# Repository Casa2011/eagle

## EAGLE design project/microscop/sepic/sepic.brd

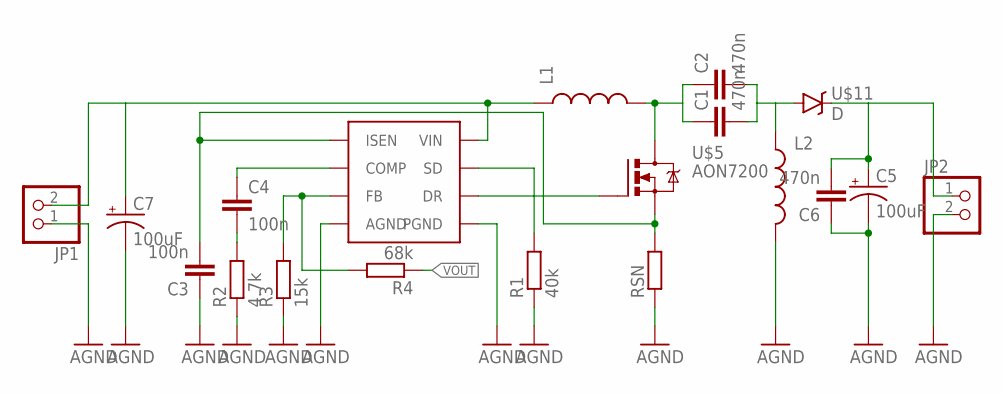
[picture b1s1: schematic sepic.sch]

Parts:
C1, C2, C6: 470n; C0805
C3, C4: 100n; C0805
C5, C7: 100uF; NIC_10X10.5_CAP
JP1, JP2: PINHD-1X02_2.54; 1X02
L1, L2: INDUCTORSRU1038; SRU1038
R1: 40k; 0603
R2: 4.7k; R0805
R3: 15k; R0805
R4: 68k; R0805
RSN: R2512
U$1: LM3488; S-PDSO-G8
U$5: AON7200; DFN3X3
U$11: D; SMA-DIODE

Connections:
AGND: C3.1, C5.-, C6.1, C7.-, JP1.1, JP2.2, L2.2, R1.1, R2.1, R3.1, RSN.P$1 (1), U$1.4 (AGND), U$1.5 (PGND)
unnamed: C3.2, RSN.P$2 (2), U$1.1 (ISEN), U$5.S:1 (S), U$5.S:2 (S), U$5.S:3 (S)
unnamed: U$1.6 (DR), U$5.G
unnamed: R1.2, U$1.7 (SD)
unnamed: C1.1, C2.1, L1.2, U$5.D, U$5.D:1 (D), U$5.D:2 (D), U$5.D:3 (D), U$5.D:4 (D), U$5.D:5 (D), U$5.D:6 (D)
unnamed: C1.2, C2.2, L2.1, U$11.A
unnamed: C4.1, U$1.2 (COMP)
unnamed: C4.2, R2.2
unnamed: R3.2, R4.2, U$1.3 (FB)
VIN: C7.+, JP1.2, L1.1, U$1.8 (VIN)
VOUT: C5.+, C6.2, JP2.1, R4.1, U$11.C

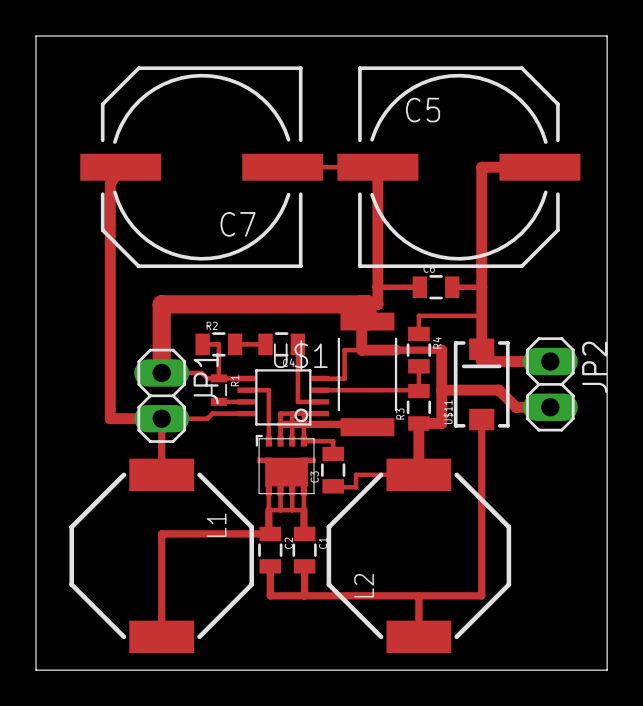
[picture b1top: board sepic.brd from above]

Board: 2 copper layers, 31.7 x 35.2 mm, 19 parts (0 on the bottom side), 11 nets.

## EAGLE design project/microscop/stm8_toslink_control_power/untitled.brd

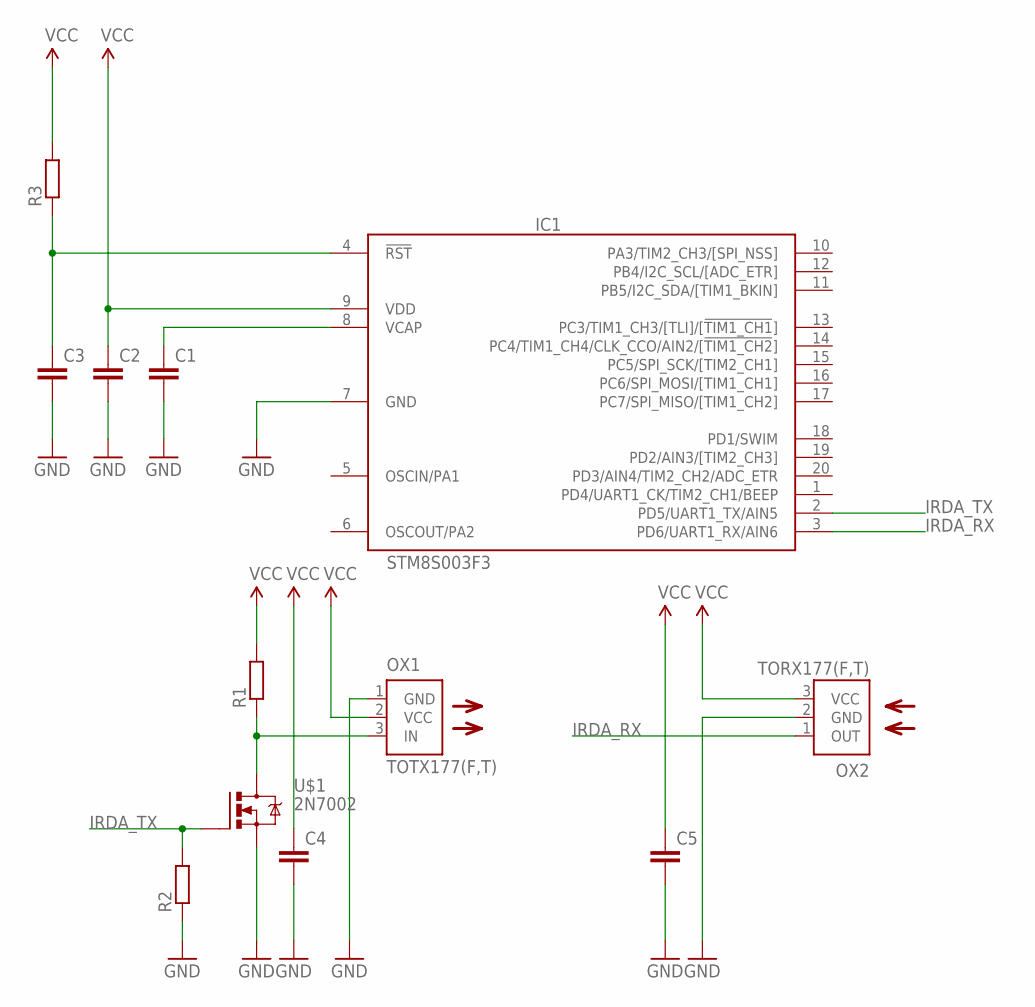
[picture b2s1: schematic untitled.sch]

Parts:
C1, C2, C4, C5: CC0805; C0805
C3: CC0603; C0603
IC1: STM8S003F3; TSSOP20
OX1: TOTX177(F,T); TOTX
OX2: TORX177(F,T); TORX
R1, R2, R3: R0603; 0603
U$1: 2N7002; SOT23

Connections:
GND: C1.2, C2.2, C3.2, C4.2, C5.2, IC1.7 (GND), OX1.1 (GND), OX2.2 (GND), R2.1, U$1.2 (S)
IRDA_RX: IC1.3 (PD6/UART1_RX/AIN6), OX2.1 (OUT)
IRDA_TX: IC1.2 (PD5/UART1_TX/AIN5), R2.2, U$1.1 (G)
unnamed: C1.1, IC1.8 (VCAP)
unnamed: OX1.3 (IN), R1.1, U$1.3 (D)
unnamed: C3.1, IC1.4 (!RST), R3.1
VCC: C2.1, C4.1, C5.1, IC1.9 (VDD), OX1.2 (VCC), OX2.3 (VCC), R1.2, R3.2

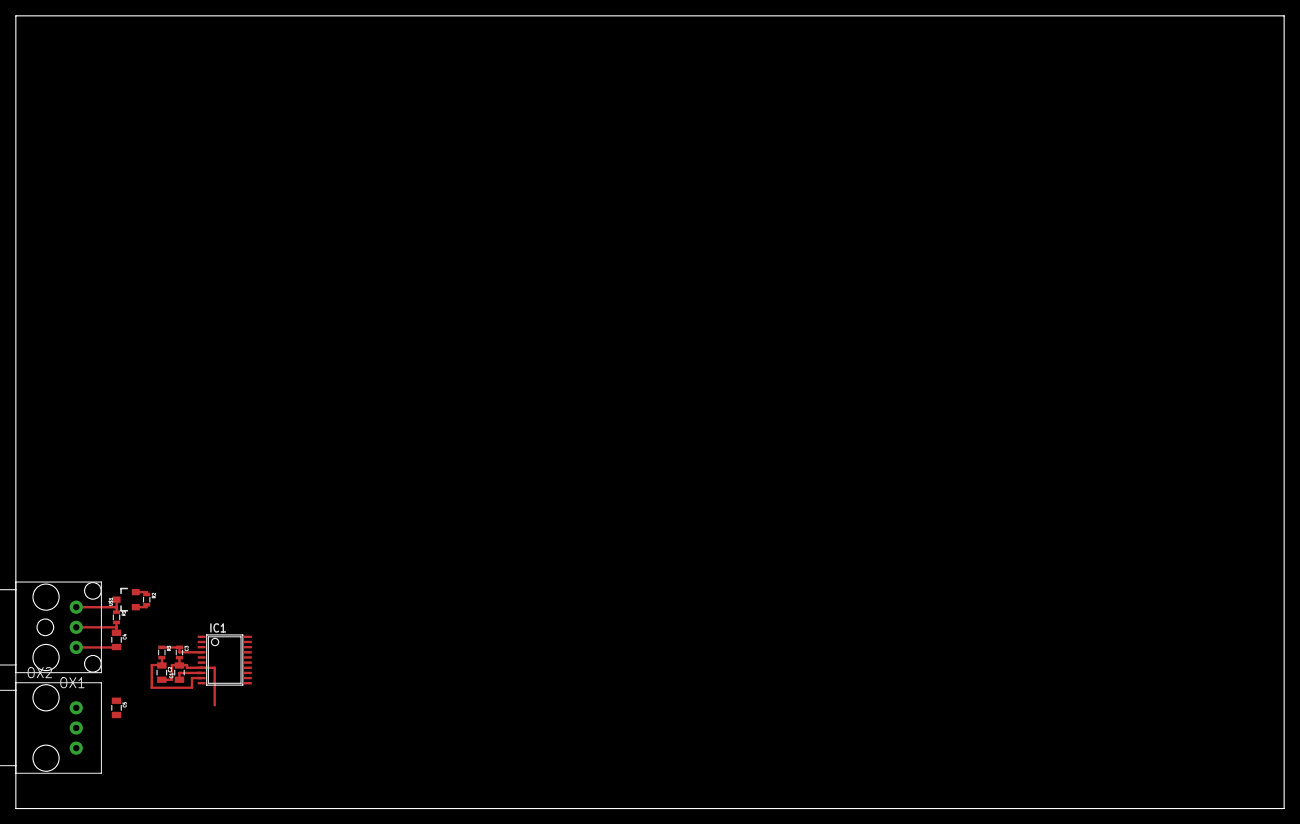
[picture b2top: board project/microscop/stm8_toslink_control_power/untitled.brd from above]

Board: 2 copper layers, 160.0 x 100.0 mm, 12 parts (0 on the bottom side), 7 nets.

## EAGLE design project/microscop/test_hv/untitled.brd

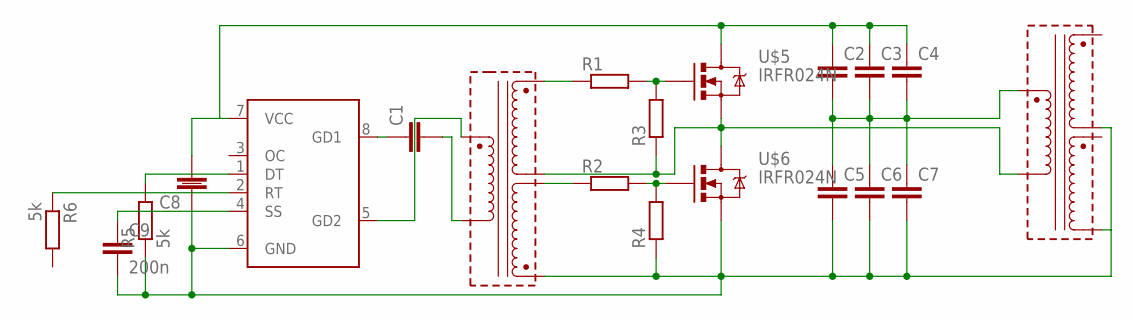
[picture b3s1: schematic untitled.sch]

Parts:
C1, C2, C3, C4, C5, C6, C7, C8: CC0805; C0805
C9: 200n; C0805
R1, R2, R3, R4: R0805
R5, R6: 5k; R0805
U$1: TPS92020; SO08
U$2: ADSL_GDT
U$3: CCFL; TRANSFORMER_HVX2
U$5, U$6: IRFR024N; D-PAK_TO252AA

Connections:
unnamed: C1.1, U$1.8 (GD1)
unnamed: C1.2, U$2.GD` (GD2)
unnamed: U$1.5 (GD2), U$2.GD (GD1)
unnamed: R1.1, U$2.OUT1 (OUT1+)
unnamed: R2.1, U$2.OUT2` (OUT2-)
unnamed: R1.2, R3.2, U$5.1 (G)
unnamed: R2.2, R4.2, U$6.1 (G)
unnamed: R3.1, U$2.OUT1` (OUT1-), U$3.P$3 (GD2), U$5.3 (S), U$6.2 (D)
unnamed: C5.2, C6.2, C7.2, C8.1, C9.2, R4.1, R5.1, U$1.6 (GND), U$2.OUT2 (OUT2+), U$3.P$6 (OUT1-), U$3.P$7 (OUT2+), U$6.3 (S)
unnamed: C2.2, C3.2, C4.2, C5.1, C6.1, C7.1, U$3.P$2 (GD1)
unnamed: C2.1, C3.1, C4.1, C8.2, U$1.7 (VCC), U$5.2 (D)
unnamed: R5.2, U$1.1 (DT)
unnamed: C9.1, U$1.4 (SS)
unnamed: R6.1, U$1.2 (RT)

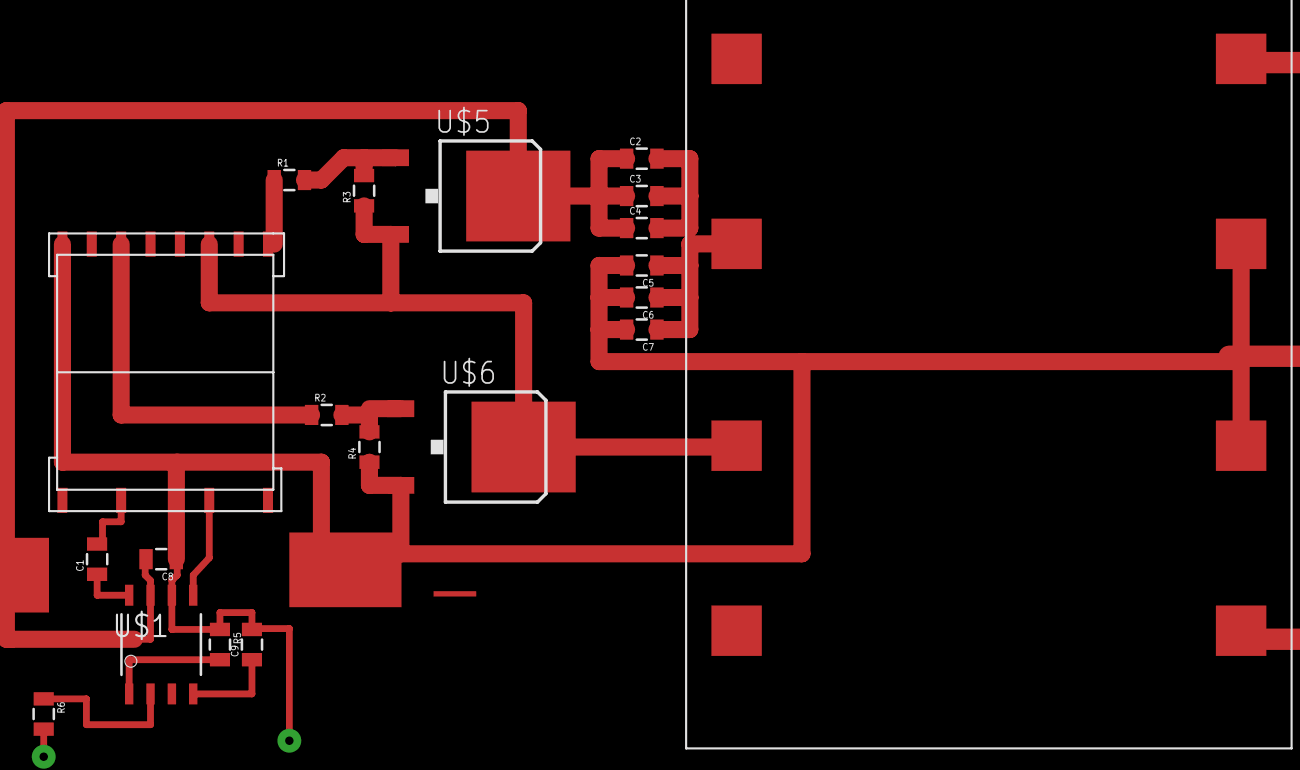
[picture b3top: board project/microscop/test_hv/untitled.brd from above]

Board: 2 copper layers, 20 parts (0 on the bottom side), 14 nets.

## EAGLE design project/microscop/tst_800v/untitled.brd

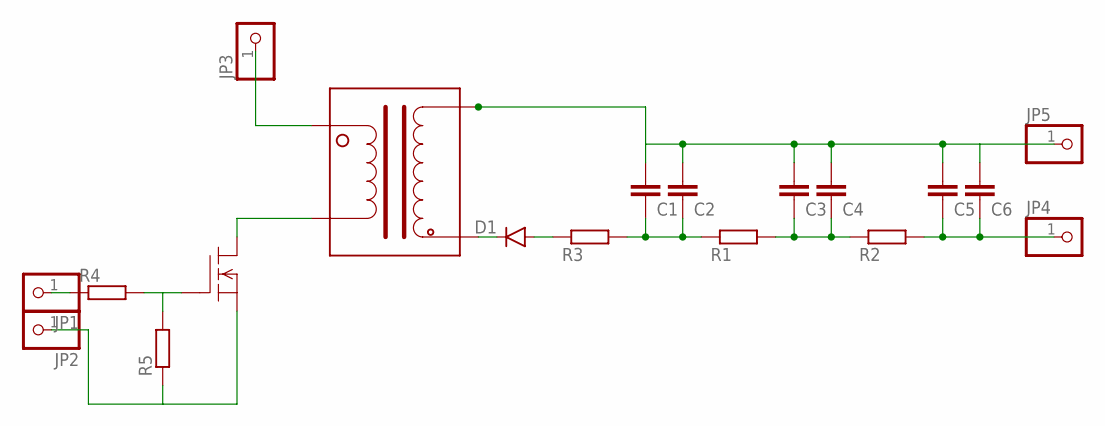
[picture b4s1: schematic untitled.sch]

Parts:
C1, C2, C3, C4, C5, C6: CC1206; C1206
D1: DIODESMA; SMA-DIODE
JP1, JP2, JP3, JP4, JP5: PINHD-1X01_2.54-90°; 1X01/90
R1, R2, R3, R4, R5: R0805
U$1: TR1
U$2: AP9402GYT-HF; SON-3X3

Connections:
unnamed: C1.1, C2.1, R1.1, R3.2
unnamed: C3.1, C4.1, R1.2, R2.1
unnamed: C5.1, C6.1, JP4.1, R2.2
unnamed: C1.2, C2.2, C3.2, C4.2, C5.2, C6.2, JP5.1, U$1.IN1 (OUT1)
unnamed: D1.A, R3.1
unnamed: D1.C, U$1.IN2 (OUT2)
unnamed: R4.2, R5.2, U$2.4 (G)
unnamed: JP3.1, U$1.OUT2 (IN2)
unnamed: U$1.OUT1 (IN1), U$2.5 (D), U$2.6 (D), U$2.7 (D), U$2.8 (D), U$2.9 (D)
unnamed: JP2.1, R5.1, U$2.1 (S), U$2.2 (S), U$2.3 (S)
unnamed: JP1.1, R4.1

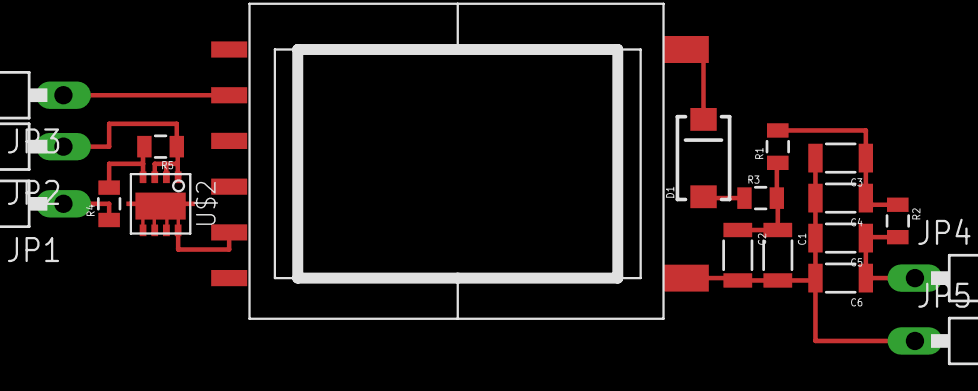
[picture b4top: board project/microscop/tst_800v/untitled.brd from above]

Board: 2 copper layers, 19 parts (0 on the bottom side), 11 nets.

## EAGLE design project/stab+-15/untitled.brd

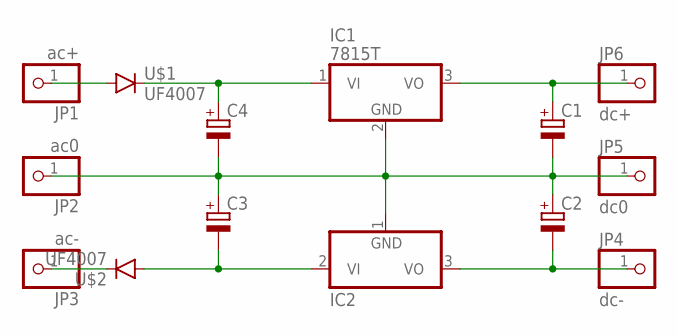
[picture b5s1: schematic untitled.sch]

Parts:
C1, C2, C3, C4: CPOL-EUE5-10.5; E5-10,5
IC1: 7815T; TO220H
IC2: 7915T; TO220H
JP1: ac+; 1X01
JP2: ac0; 1X01
JP3: ac-; 1X01
JP4: dc-; 1X01
JP5: dc0; 1X01
JP6: dc+; 1X01
U$1, U$2: UF4007; SMA-DIODE

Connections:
unnamed: C1.-, C2.+, C3.+, C4.-, IC1.2 (GND), IC2.1 (GND), JP2.1, JP5.1
unnamed: C1.+, IC1.3 (VO), JP6.1
unnamed: C2.-, IC2.3 (VO), JP4.1
unnamed: C4.+, IC1.1 (VI), U$1.C
unnamed: C3.-, IC2.2 (VI), U$2.A
unnamed: JP1.1, U$1.A
unnamed: JP3.1, U$2.C

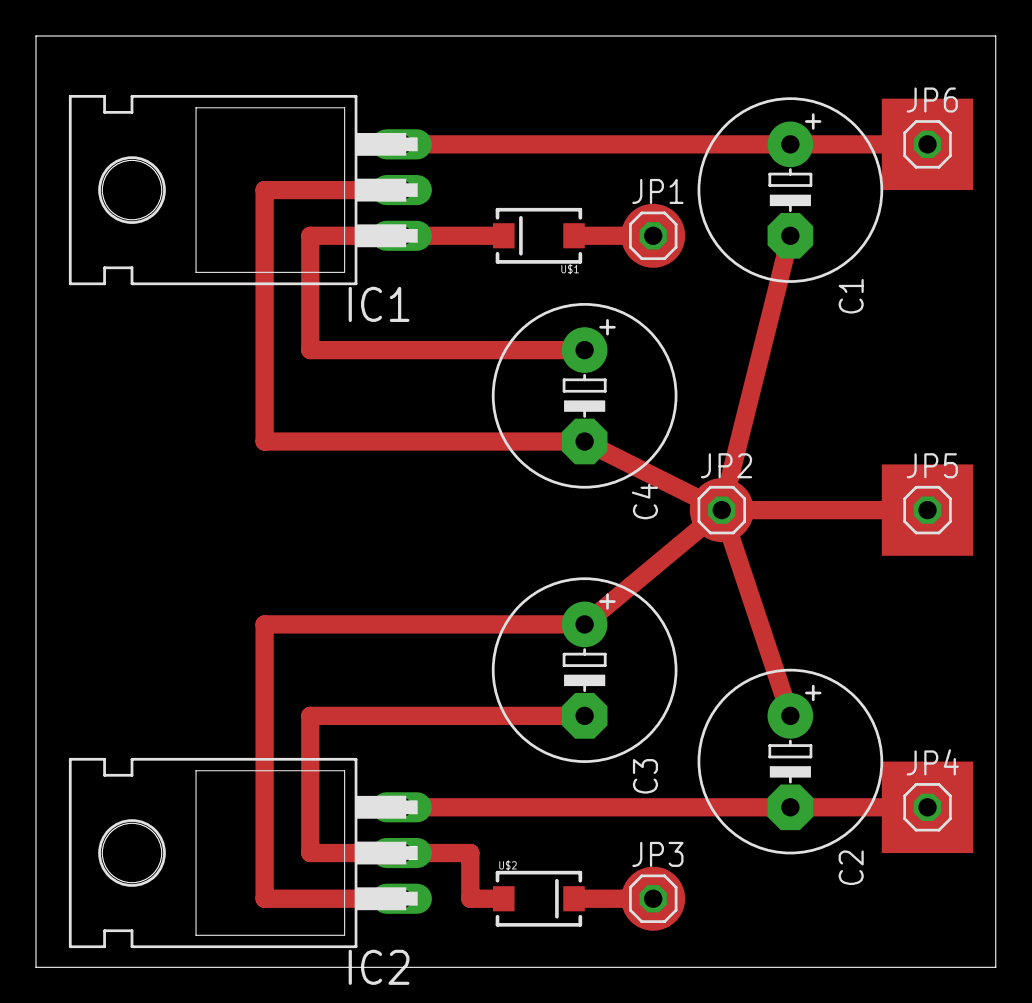
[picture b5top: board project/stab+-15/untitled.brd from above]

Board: 2 copper layers, 53.3 x 51.7 mm, 14 parts (0 on the bottom side), 7 nets.

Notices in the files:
parts and their libraries:
SparkFun-FreqCtrl: Licensing: Creative Commons ShareAlike 4.0 International - https://creativecommons.org/licenses/by-sa/4.0
